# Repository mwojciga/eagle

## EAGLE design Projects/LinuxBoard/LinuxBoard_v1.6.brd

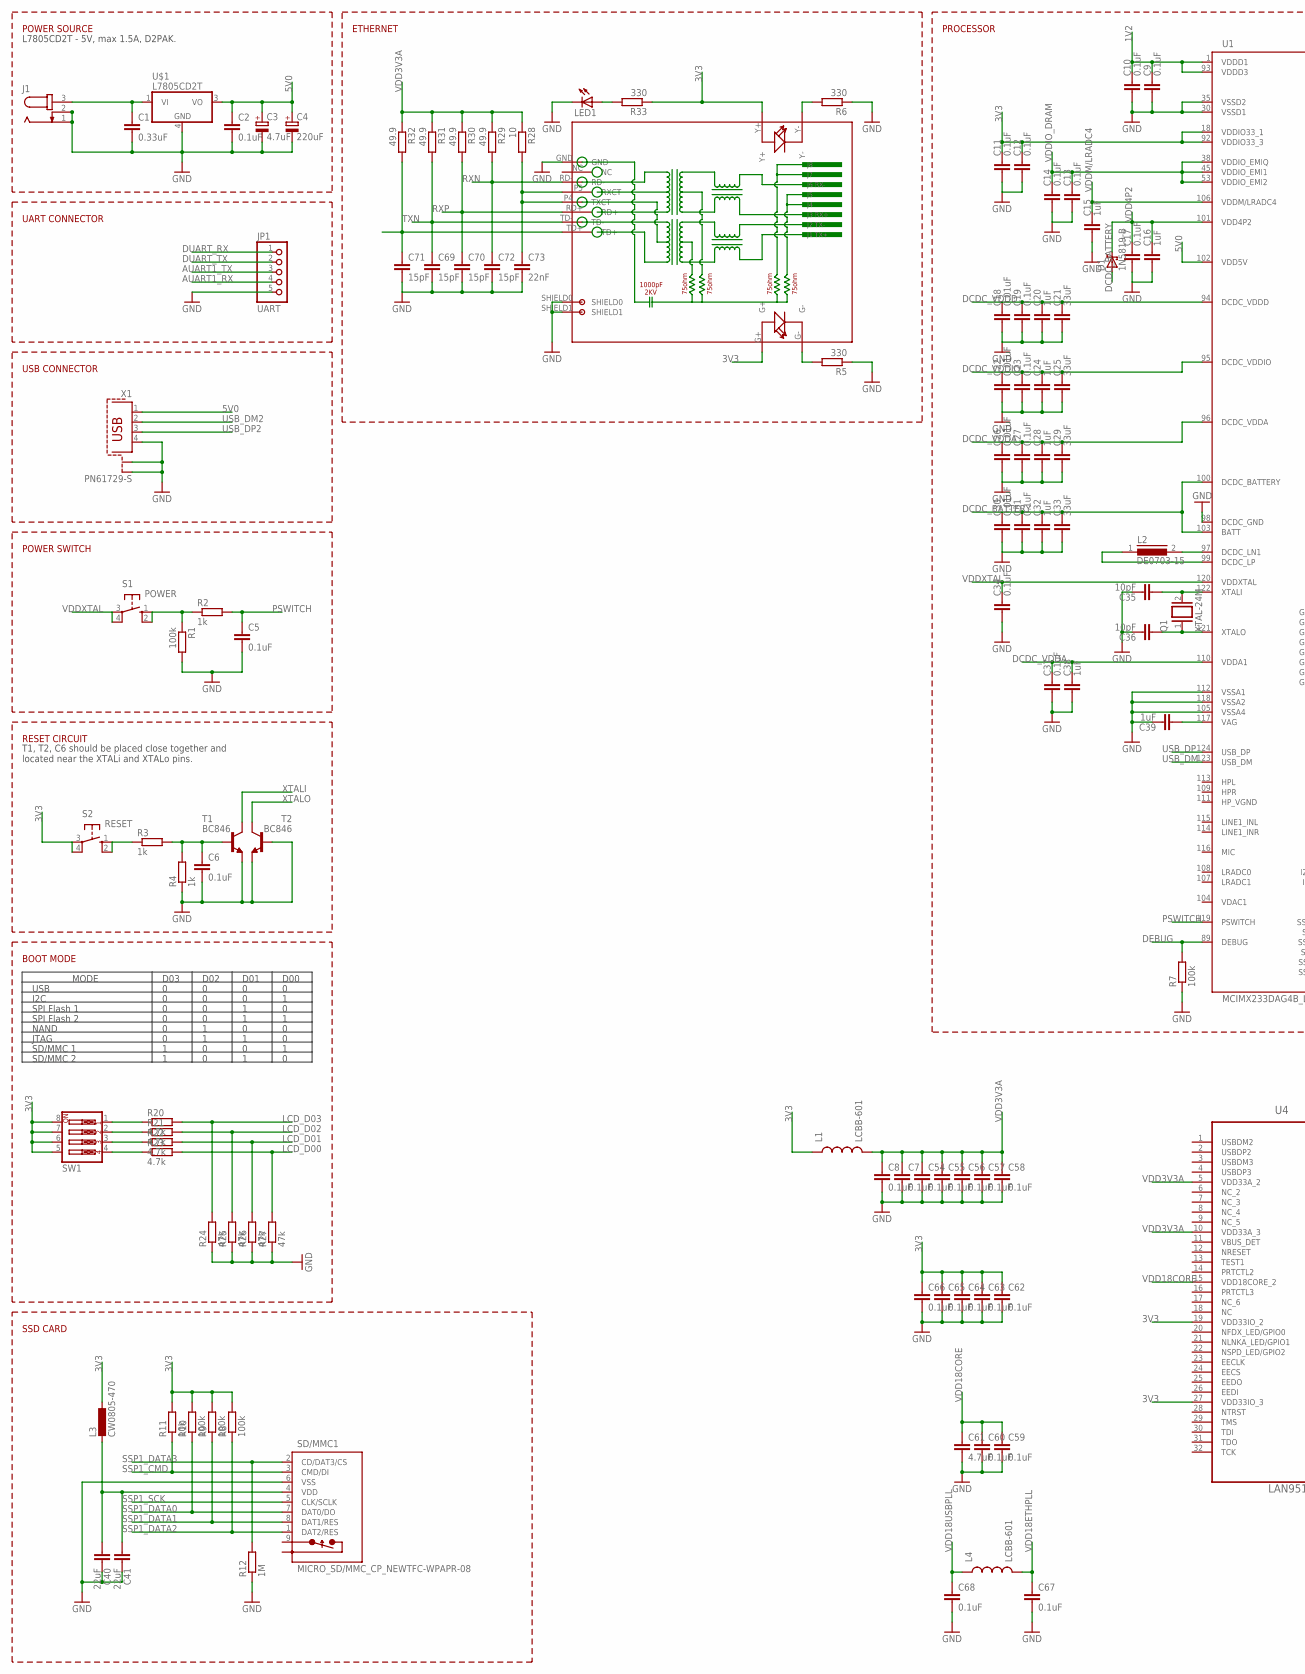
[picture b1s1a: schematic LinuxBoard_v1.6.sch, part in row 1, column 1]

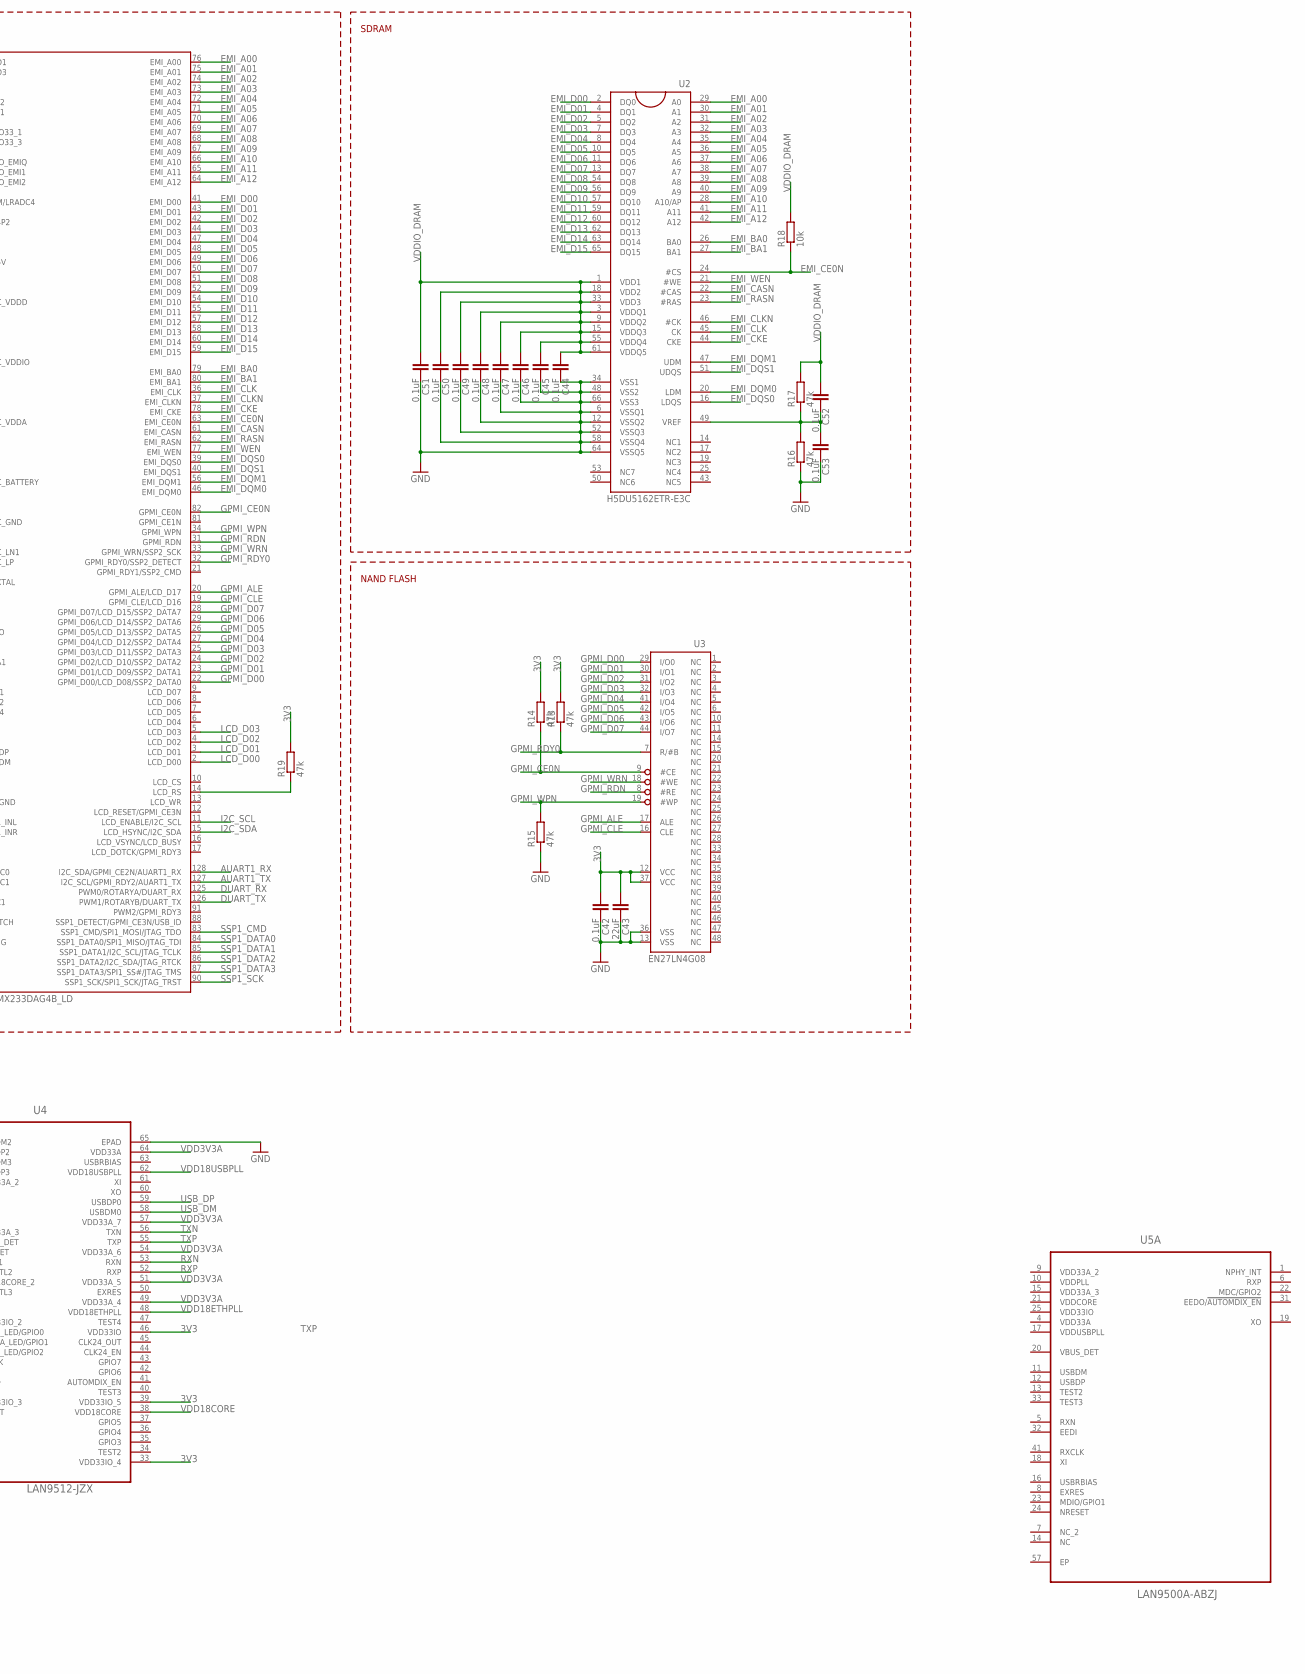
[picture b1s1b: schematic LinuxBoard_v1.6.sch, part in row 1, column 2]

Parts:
C1: 0.33uF; C0805
C2, C5, C6, C7, C8, C9, C10, C11, C12, C13, C14, C17, C19, C23, C27, C31, C34, C37, C42, C44, C45, C46, C47, C48, C49, C50, C51, C52, C53, C54, C55, C56, C57, C58, C59, C60, C62, C63, C64, C65, C66, C67, C68: 0.1uF; C0805
C3: 4.7uF; E2-5
C4: 220uF; E2-5
C15, C16, C20, C24, C28, C32, C38, C39: 1uF; C0805
C18, C22, C26, C30: 0.01uF; C0805
C21, C25, C29, C33: 33uF; C0805
C35, C36: 10pF; C0805
C40, C41, C43: 22uF; C0805
C61: 4.7uF; C0805
C69, C70, C71, C72: 15pF; C0805
C73: 22nF; C0805
D1: 1N5819-B; DO41-7.6
J1: JACK-PLUG0; SPC4077
JP1: UART; 1X05
L1, L4: LCBB-601; 0805
L2: DE0703-15; DR73
L3: CW0805-470; L2012C
LED1: LEDSML0805; SML0805
Q1: XTAL-24M; QS
R1, R7, R8, R9, R10: 100k; R0805
R2, R3, R4: 1k; R0805
R5, R6, R33: 330; R0805
R11, R18: 10k; R0805
R12: 1M; R0805
R13, R14, R15, R16, R17, R19, R24, R25, R26, R27: 47k; R0805
R20, R21, R22, R23: 4.7k; R0805
R28: 10; R0805
R29, R30, R31, R32: 49.9; R0805
RJ1: HR911105A
S1: POWER; B3F-10XX
S2: RESET; B3F-10XX
SD/MMC1: MICRO_SD/MMC_CP_NEWTFC-WPAPR-08; TFC-WPAPR-08
SW1: SW_DIP-4; EDG-04
T1, T2: BC846; SOT23
U1: MCIMX233DAG4B_LD; TQFP128LD
U2: H5DU5162ETR-E3C; 66TSOP-II
U3: EN27LN4G08; TSOP48
U4: LAN9512-JZX; QFN50P900X900X100-65N
U5: LAN9500A-ABZJ; QFN50P800X800X100-57N
U$1: L7805CD2T; D2PAK-3
X1: PN61729-S

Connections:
1V2: C9.1, C10.1, U1.1 (VDDD1), U1.93 (VDDD3)
3V3: C11.1, C12.1, C42.2, C43.2, C62.1, C63.1, C64.1, C65.1, C66.1, L1.1, L3.1, R8.2, R9.2, R10.2, R11.2, R13.2, R14.2, R19.2, R33.1, RJ1.G+, RJ1.Y+, S2.3, S2.4 (P1), SW1.5, SW1.6, SW1.7, SW1.8, U1.18 (VDDIO33_1), U1.92 (VDDIO33_3), U3.12 (VCC), U3.37 (VCC), U4.19 (VDD33IO_2), U4.27 (VDD33IO_3), U4.33 (VDD33IO_4), U4.39 (VDD33IO_5), U4.46 (VDD33IO)
5V0: C2.1, C3.+, C4.+, U1.102 (VDD5V), U$1.3 (VO), X1.1
AUART1_RX: JP1.4, U1.128 (I2C_SDA/GPMI_CE2N/AUART1_RX)
AUART1_TX: JP1.3, U1.127 (I2C_SCL/GPMI_RDY2/AUART1_TX)
DCDC_BATTERY: C30.1, C31.1, C32.1, C33.1, D1.A, U1.100 (DCDC_BATTERY), U1.103 (BATT)
DCDC_VDDA: C26.1, C27.1, C28.1, C29.1, C37.1, C38.1, U1.96 (DCDC_VDDA), U1.110 (VDDA1)
DCDC_VDDD: C18.1, C19.1, C20.1, C21.1, U1.94 (DCDC_VDDD)
DCDC_VDDIO: C22.1, C23.1, C24.1, C25.1, U1.95 (DCDC_VDDIO)
DEBUG: R7.2, U1.89 (DEBUG)
DUART_RX: JP1.1, U1.125 (PWM0/ROTARYA/DUART_RX)
DUART_TX: JP1.2, U1.126 (PWM1/ROTARYB/DUART_TX)
EMI_A00: U1.76 (EMI_A00), U2.29 (A0)
EMI_A01: U1.75 (EMI_A01), U2.30 (A1)
EMI_A02: U1.74 (EMI_A02), U2.31 (A2)
EMI_A03: U1.73 (EMI_A03), U2.32 (A3)
EMI_A04: U1.72 (EMI_A04), U2.35 (A4)
EMI_A05: U1.71 (EMI_A05), U2.36 (A5)
EMI_A06: U1.70 (EMI_A06), U2.37 (A6)
EMI_A07: U1.69 (EMI_A07), U2.38 (A7)
EMI_A08: U1.68 (EMI_A08), U2.39 (A8)
EMI_A09: U1.67 (EMI_A09), U2.40 (A9)
EMI_A10: U1.66 (EMI_A10), U2.28 (A10/AP)
EMI_A11: U1.65 (EMI_A11), U2.41 (A11)
EMI_A12: U1.64 (EMI_A12), U2.42 (A12)
EMI_BA0: U1.79 (EMI_BA0), U2.26 (BA0)
EMI_BA1: U1.80 (EMI_BA1), U2.27 (BA1)
EMI_CASN: U1.61 (EMI_CASN), U2.22 (#CAS)
EMI_CE0N: R18.1, U1.63 (EMI_CE0N), U2.24 (#CS)
EMI_CKE: U1.78 (EMI_CKE), U2.44 (CKE)
EMI_CLK: U1.36 (EMI_CLK), U2.45 (CK)
EMI_CLKN: U1.37 (EMI_CLKN), U2.46 (#CK)
EMI_D00: U1.41 (EMI_D00), U2.2 (DQ0)
EMI_D01: U1.43 (EMI_D01), U2.4 (DQ1)
EMI_D02: U1.42 (EMI_D02), U2.5 (DQ2)
EMI_D03: U1.44 (EMI_D03), U2.7 (DQ3)
EMI_D04: U1.47 (EMI_D04), U2.8 (DQ4)
EMI_D05: U1.48 (EMI_D05), U2.10 (DQ5)
EMI_D06: U1.49 (EMI_D06), U2.11 (DQ6)
EMI_D07: U1.50 (EMI_D07), U2.13 (DQ7)
EMI_D08: U1.51 (EMI_D08), U2.54 (DQ8)
EMI_D09: U1.52 (EMI_D09), U2.56 (DQ9)
EMI_D10: U1.54 (EMI_D10), U2.57 (DQ10)
EMI_D11: U1.55 (EMI_D11), U2.59 (DQ11)
EMI_D12: U1.57 (EMI_D12), U2.60 (DQ12)
EMI_D13: U1.58 (EMI_D13), U2.62 (DQ13)
EMI_D14: U1.60 (EMI_D14), U2.63 (DQ14)
EMI_D15: U1.59 (EMI_D15), U2.65 (DQ15)
EMI_DQM0: U1.46 (EMI_DQM0), U2.20 (LDM)
EMI_DQM1: U1.56 (EMI_DQM1), U2.47 (UDM)
EMI_DQS0: U1.39 (EMI_DQS0), U2.16 (LDQS)
EMI_DQS1: U1.40 (EMI_DQS1), U2.51 (UDQS)
EMI_RASN: U1.62 (EMI_RASN), U2.23 (#RAS)
EMI_WEN: U1.77 (EMI_WEN), U2.21 (#WE)
GND: C1.2, C2.2, C3.-, C4.-, C5.2, C6.2, C7.2, C8.2, C9.2, C10.2, C11.2, C12.2, C13.2, C14.2, C15.2, C16.2, C17.2, C18.2, C19.2, C20.2, C21.2, C22.2, C23.2, C24.2, C25.2, C26.2, C27.2, C28.2, C29.2, C30.2, C31.2, C32.2, C33.2, C34.2, C35.1, C36.1, C37.2, C38.2, C39.1, C40.1, C41.1, C42.1, C43.1, C44.1, C45.1, C46.1, C47.1, C48.1, C49.1, C50.1, C51.1, C53.1, C54.2, C55.2, C56.2, C57.2, C58.2, C59.2, C60.2, C61.2, C62.2, C63.2, C64.2, C65.2, C66.2, C67.2, C68.2, C69.2, C70.2, C71.2, C72.2, C73.2, J1.1, J1.2, JP1.5, LED1.C, R1.2, R4.1, R5.1, R6.1, R7.1, R12.1, R15.1, R16.1, R24.1, R25.1, R26.1, R27.1, RJ1.GND, RJ1.SHIELD0, RJ1.SHIELD1, SD/MMC1.6 (VSS), T1.2 (E), T2.1 (B), T2.2 (E), U1.30 (VSSD1), U1.35 (VSSD2), U1.98 (DCDC_GND), U1.105 (VSSA4), U1.112 (VSSA1), U1.118 (VSSA2), U2.6 (VSSQ1), U2.12 (VSSQ2), U2.34 (VSS1), U2.48 (VSS2), U2.52 (VSSQ3), U2.58 (VSSQ4), U2.64 (VSSQ5), U2.66 (VSS3), U3.13 (VSS), U3.36 (VSS), U4.65 (EPAD), U$1.4 (GND), X1.4, X1.S1, X1.S2
GPMI_ALE: U1.20 (GPMI_ALE/LCD_D17), U3.17 (ALE)
GPMI_CE0N: R14.1, U1.82 (GPMI_CE0N), U3.9 (#CE)
GPMI_CLE: U1.19 (GPMI_CLE/LCD_D16), U3.16 (CLE)
GPMI_D00: U1.22 (GPMI_D00/LCD_D08/SSP2_DATA0), U3.29 (I/O0)
GPMI_D01: U1.23 (GPMI_D01/LCD_D09/SSP2_DATA1), U3.30 (I/O1)
GPMI_D02: U1.24 (GPMI_D02/LCD_D10/SSP2_DATA2), U3.31 (I/O2)
GPMI_D03: U1.25 (GPMI_D03/LCD_D11/SSP2_DATA3), U3.32 (I/O3)
GPMI_D04: U1.27 (GPMI_D04/LCD_D12/SSP2_DATA4), U3.41 (I/O4)
GPMI_D05: U1.26 (GPMI_D05/LCD_D13/SSP2_DATA5), U3.42 (I/O5)
GPMI_D06: U1.29 (GPMI_D06/LCD_D14/SSP2_DATA6), U3.43 (I/O6)
GPMI_D07: U1.28 (GPMI_D07/LCD_D15/SSP2_DATA7), U3.44 (I/O7)
GPMI_RDN: U1.31 (GPMI_RDN), U3.8 (#RE)
GPMI_RDY0: R13.1, U1.32 (GPMI_RDY0/SSP2_DETECT), U3.7 (R/#B)
GPMI_WPN: R15.2, U1.34 (GPMI_WPN), U3.19 (#WP)
GPMI_WRN: U1.33 (GPMI_WRN/SSP2_SCK), U3.18 (#WE)
HP_VGND: U1.111 (HP_VGND)
I2C_SCL: U1.11 (LCD_ENABLE/I2C_SCL)
I2C_SDA: U1.15 (LCD_HSYNC/I2C_SDA)
LCD_D00: R23.2, R27.2, U1.2 (LCD_D00)
LCD_D01: R22.2, R26.2, U1.3 (LCD_D01)
LCD_D02: R21.2, R25.2, U1.4 (LCD_D02)
LCD_D03: R20.2, R24.2, U1.5 (LCD_D03)
unnamed: C1.1, J1.3, U$1.1 (VI)
unnamed: R3.1, S2.1 (S), S2.2 (S1)
unnamed: R1.1, R2.1, S1.1 (S), S1.2 (S1)
unnamed: C6.1, R3.2, R4.2, T1.1 (B)
unnamed: R20.1, SW1.1
unnamed: R21.1, SW1.2
unnamed: R22.1, SW1.3
unnamed: R23.1, SW1.4
unnamed: L2.2, U1.97 (DCDC_LN1)
unnamed: R5.2, RJ1.G-
unnamed: L2.1, U1.99 (DCDC_LP)
unnamed: C39.2, U1.117 (VAG)
unnamed: R19.1, U1.14 (LCD_RS)
unnamed: R6.2, RJ1.Y-
unnamed: C40.2, C41.2, L3.2, SD/MMC1.4 (VDD)
unnamed: C73.1, R28.2, RJ1.P4 (TXCT), RJ1.P5 (RXCT)
unnamed: LED1.A, R33.2
unnamed: C52.1, C53.2, R16.2, R17.1, U2.49 (VREF)
PSWITCH: C5.1, R2.2, U1.119 (PSWITCH)
RXN: C72.1, R29.2, RJ1.RD-, U4.53 (RXN)
RXP: C70.1, R30.2, RJ1.RD+, U4.52 (RXP)
SSP1_CMD: R11.1, SD/MMC1.3 (CMD/DI), U1.83 (SSP1_CMD/SPI1_MOSI/JTAG_TDO)
SSP1_DATA0: R10.1, SD/MMC1.7 (DAT0/DO), U1.84 (SSP1_DATA0/SPI1_MISO/JTAG_TDI)
SSP1_DATA1: R9.1, SD/MMC1.8 (DAT1/RES), U1.85 (SSP1_DATA1/I2C_SCL/JTAG_TCLK)
SSP1_DATA2: R8.1, SD/MMC1.1 (DAT2/RES), U1.86 (SSP1_DATA2/I2C_SDA/JTAG_RTCK)
SSP1_DATA3: R12.2, SD/MMC1.2 (CD/DAT3/CS), U1.87 (SSP1_DATA3/SPI1_SS#/JTAG_TMS)
SSP1_SCK: SD/MMC1.5 (CLK/SCLK), U1.90 (SSP1_SCK/SPI1_SCK/JTAG_TRST)
TEST1: U5.49 (TEST1)
TEST2: U5.13 (TEST2)
TEST3: U5.33 (TEST3)
TXN: C69.1, R31.2, RJ1.TD-, U4.56 (TXN)
TXP: C71.1, R32.2, RJ1.TD+, U4.55 (TXP)
USB_DM: U1.123 (USB_DM), U4.58 (USBDM0)
USB_DM2: X1.2
USB_DP: U1.124 (USB_DP), U4.59 (USBDP0)
USB_DP2: X1.3
VBUS_DET: U4.11 (VBUS_DET), U5.20 (VBUS_DET)
VDD3V3A: C7.1, C8.1, C54.1, C55.1, C56.1, C57.1, C58.1, L1.2, R28.1, R29.1, R30.1, R31.1, R32.1, U4.5 (VDD33A_2), U4.10 (VDD33A_3), U4.49 (VDD33A_4), U4.51 (VDD33A_5), U4.54 (VDD33A_6), U4.57 (VDD33A_7), U4.64 (VDD33A), U5.4 (VDD33A)
VDD4P2: C16.1, C17.1, D1.C, U1.101 (VDD4P2)
VDD18CORE: C59.1, C60.1, C61.1, U4.15 (VDD18CORE_2), U4.38 (VDD18CORE)
VDD18ETHPLL: C67.1, L4.2, U4.48 (VDD18ETHPLL)
VDD18USBPLL: C68.1, L4.1, U4.62 (VDD18USBPLL)
VDD33A_2: U5.9 (VDD33A_2)
VDD33A_3: U5.15 (VDD33A_3)
VDD33IO: U5.25 (VDD33IO), U5.52 (VDD33IO)
VDD33IO_2: U5.48 (VDD33IO_2)
VDD33IO_3: U5.51 (VDD33IO_3)
VDD33IO_4: U5.35 (VDD33IO_4)
VDDCORE: U5.50 (VDDCORE)
VDDIO_DRAM: C13.1, C14.1, C44.2, C45.2, C46.2, C47.2, C48.2, C49.2, C50.2, C51.2, C52.2, R17.2, R18.2, U1.38 (VDDIO_EMIQ), U1.45 (VDDIO_EMI1), U1.53 (VDDIO_EMI2), U2.1 (VDD1), U2.3 (VDDQ1), U2.9 (VDDQ2), U2.15 (VDDQ3), U2.18 (VDD2), U2.33 (VDD3), U2.55 (VDDQ4), U2.61 (VDDQ5)
VDDM/LRADC4: C15.1, U1.106 (VDDM/LRADC4)
VDDPLL: U5.10 (VDDPLL)
VDDUSBPLL: U5.17 (VDDUSBPLL)
VDDXTAL: C34.1, S1.3, S1.4 (P1), U1.120 (VDDXTAL)
XTALI: C35.2, Q1.2, T1.3 (C), U1.122 (XTALI)
XTALO: C36.2, Q1.1, T2.3 (C), U1.121 (XTALO)

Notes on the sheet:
L7805CD2T - 5V, max 1.5A, D2PAK.
POWER SOURCE
UART CONNECTOR
USB CONNECTOR
POWER SWITCH
RESET CIRCUIT
T1, T2, C6 should be placed close together and located near the XTALi and XTALo pins.
BOOT MODE
MODE
D03
D02
D01
D00
USB
I2C
SPI Flash 1
SPI Flash 2
NAND
JTAG
SD/MMC 1
SD/MMC 2
SSD CARD
SDRAM
NAND FLASH
ETHERNET
PROCESSOR

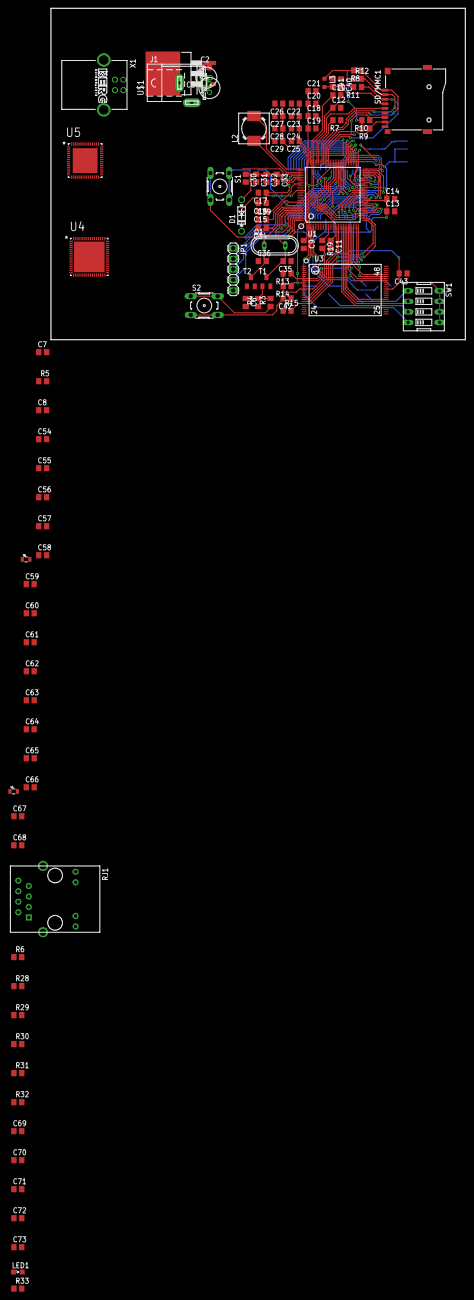
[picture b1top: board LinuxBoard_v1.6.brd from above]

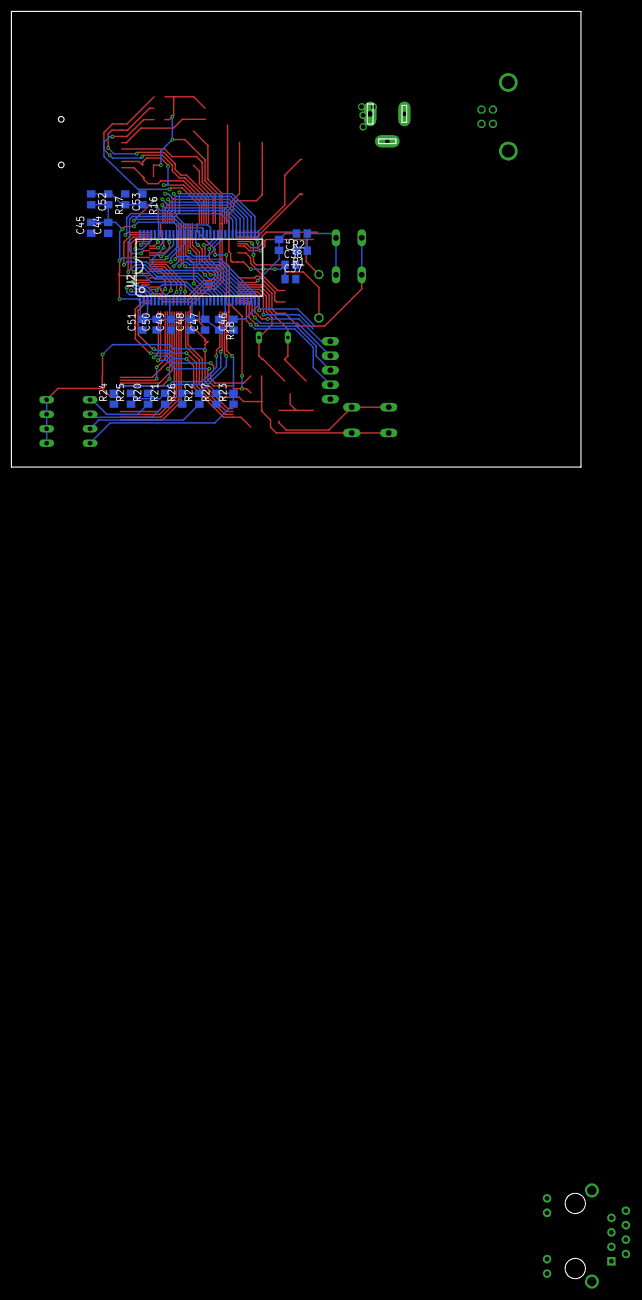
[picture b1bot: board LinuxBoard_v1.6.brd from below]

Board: 2 copper layers, 100.0 x 80.0 mm, 129 parts (27 on the bottom side), 117 nets.

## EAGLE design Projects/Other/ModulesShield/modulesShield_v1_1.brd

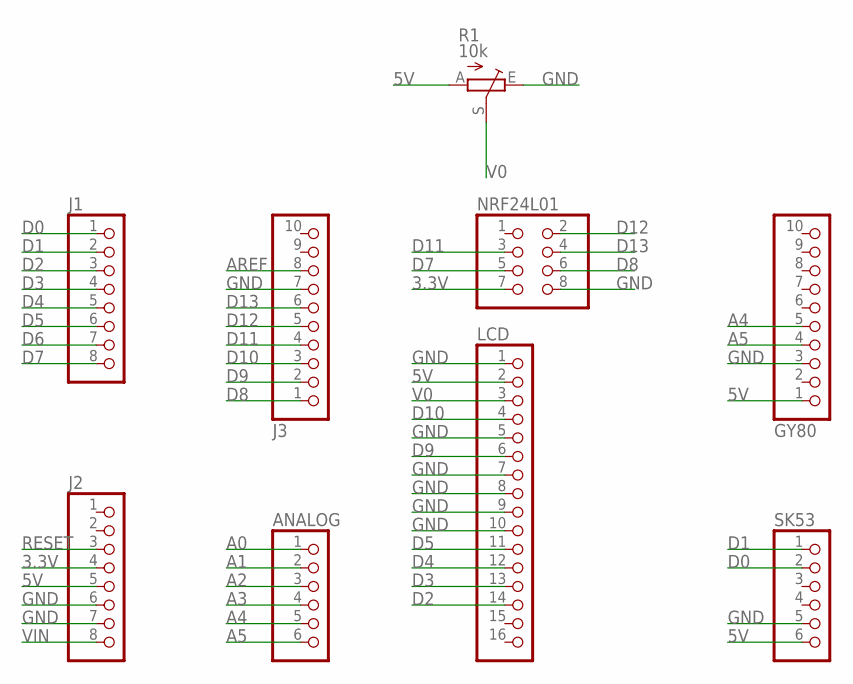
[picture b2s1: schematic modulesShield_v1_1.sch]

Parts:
ANALOG: PINHD-1X6; 1X06
GY80: PINHD-1X10TH; 1X10-TH
J1, J2: PINHD-1X8TH; 1X08-TH
J3: PINHD-1X10TH; 1X10-TH
LCD: PINHD-1X16; 1X16
NRF24L01: PINHD-2X4; 2X04
R1: 10k; CA6V
SK53: PINHD-1X6; 1X06

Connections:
3.3V: J2.4, NRF24L01.7
5V: GY80.1, J2.5, LCD.2, R1.A, SK53.6
A0: ANALOG.1
A1: ANALOG.2
A2: ANALOG.3
A3: ANALOG.4
A4: ANALOG.5, GY80.5
A5: ANALOG.6, GY80.4
AREF: J3.8
D0: J1.1, SK53.2
D1: J1.2, SK53.1
D2: J1.3, LCD.14
D3: J1.4, LCD.13
D4: J1.5, LCD.12
D5: J1.6, LCD.11
D6: J1.7
D7: J1.8, NRF24L01.5
D8: J3.1, NRF24L01.6
D9: J3.2, LCD.6
D10: J3.3, LCD.4
D11: J3.4, NRF24L01.3
D12: J3.5, NRF24L01.2
D13: J3.6, NRF24L01.4
GND: GY80.3, J2.6, J2.7, J3.7, LCD.1, LCD.5, LCD.7, LCD.8, LCD.9, LCD.10, NRF24L01.8, R1.E, SK53.5
RESET: J2.3
V0: LCD.3, R1.S
VIN: J2.8

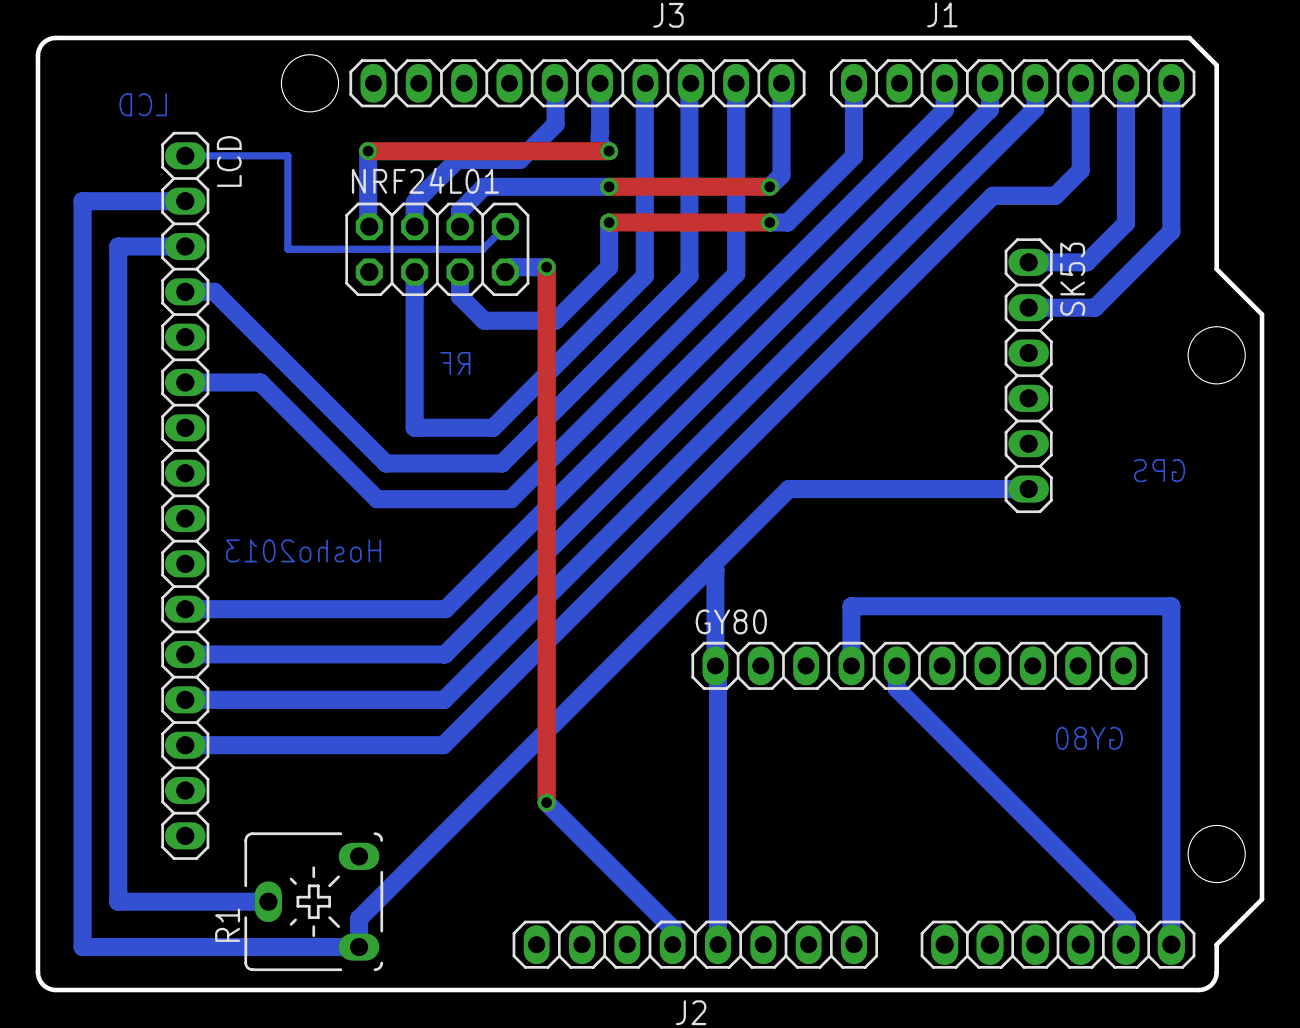
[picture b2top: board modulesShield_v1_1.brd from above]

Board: 2 copper layers, 68.6 x 53.3 mm, 9 parts (0 on the bottom side), 19 nets.

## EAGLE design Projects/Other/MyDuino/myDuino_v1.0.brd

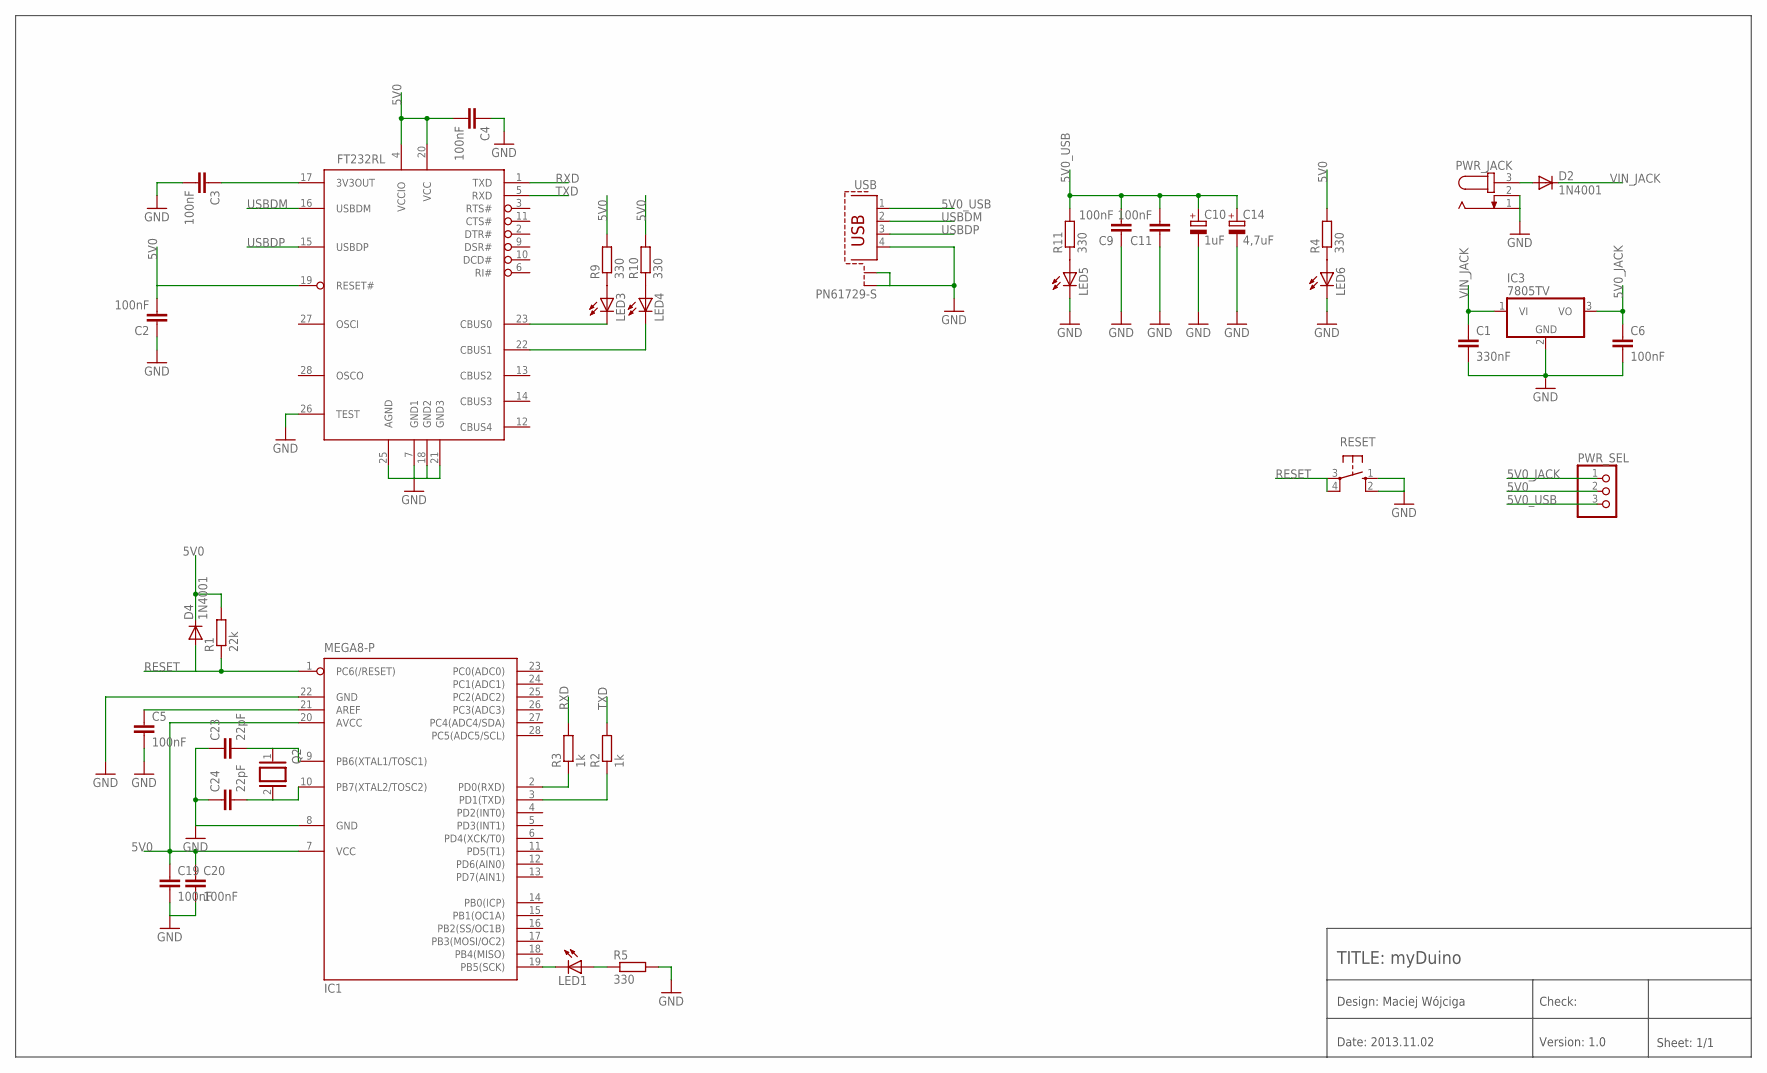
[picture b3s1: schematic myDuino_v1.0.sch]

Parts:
C1: 330nF; C025-025X050
C2, C3, C4, C5, C6, C9, C11, C19, C20: 100nF; C025-025X050
C10: 1uF; E2,5-5
C14: 4,7uF; E2,5-5
C23, C24: 22pF; C025-025X050
D2, D4: 1N4001; DO41-10
FT232RL: FT232RL; SSOP28DB
IC1: MEGA8-P; DIL28-3
IC3: 7805TV; TO220V
LED1, LED3, LED4, LED5, LED6: LED3MM
PWR_JACK: JACK-PLUG0; SPC4077
PWR_SEL: PINHD-1X3; 1X03
Q2: XTAL/S; QS
R1: 22k; 0207/10
R2, R3: 1k; 0207/10
R4, R5, R9, R10, R11: 330; 0207/10
RESET: 10-XX; B3F-10XX
USB: PN61729-S

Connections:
5V0: C2.2, C4.2, C19.1, C20.1, D4.C, FT232RL.4 (VCCIO), FT232RL.19 (RESET#), FT232RL.20 (VCC), IC1.7 (VCC), IC1.20 (AVCC), PWR_SEL.2, R1.2, R4.2, R9.2, R10.2
5V0_JACK: C6.1, IC3.3 (VO), PWR_SEL.1
5V0_USB: C9.2, C10.+, C11.2, C14.+, PWR_SEL.3, R11.2, USB.1
GND: C1.2, C2.1, C3.2, C4.1, C5.2, C6.2, C9.1, C10.-, C11.1, C14.-, C19.2, C20.2, C23.1, C24.1, FT232RL.7 (GND1), FT232RL.18 (GND2), FT232RL.21 (GND3), FT232RL.25 (AGND), FT232RL.26 (TEST), IC1.8 (GND), IC1.22 (GND), IC3.2 (GND), LED5.K (C), LED6.K (C), PWR_JACK.1, PWR_JACK.2, R5.2, RESET.1 (S), RESET.2 (S1), USB.4, USB.S1, USB.S2
unnamed: IC1.3 (PD1(TXD)), R2.1
unnamed: IC1.2 (PD0(RXD)), R3.1
unnamed: LED6.A, R4.1
unnamed: D2.A, PWR_JACK.3
unnamed: LED1.A, R5.1
unnamed: IC1.19 (PB5(SCK)), LED1.K (C)
unnamed: LED3.A, R9.1
unnamed: LED4.A, R10.1
unnamed: LED5.A, R11.1
unnamed: C5.1, IC1.21 (AREF)
unnamed: C23.2, IC1.9 (PB6(XTAL1/TOSC1)), Q2.1
unnamed: C24.2, IC1.10 (PB7(XTAL2/TOSC2)), Q2.2
unnamed: FT232RL.23 (CBUS0), LED3.K (C)
unnamed: FT232RL.22 (CBUS1), LED4.K (C)
unnamed: C3.1, FT232RL.17 (3V3OUT)
RESET: D4.A, IC1.1 (PC6(/RESET)), R1.1, RESET.3, RESET.4 (P1)
RXD: FT232RL.1 (TXD), R3.2
TXD: FT232RL.5 (RXD), R2.2
USBDM: FT232RL.16 (USBDM), USB.2
USBDP: FT232RL.15 (USBDP), USB.3
VIN_JACK: C1.1, D2.C, IC3.1 (VI)

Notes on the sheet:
TITLE: myDuino
Design: Maciej Wójciga
Check:
Date: 2013.11.02
Version: 1.0
Sheet: 1/1

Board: 2 copper layers, 37 parts (0 on the bottom side), 25 nets, no tracks yet.

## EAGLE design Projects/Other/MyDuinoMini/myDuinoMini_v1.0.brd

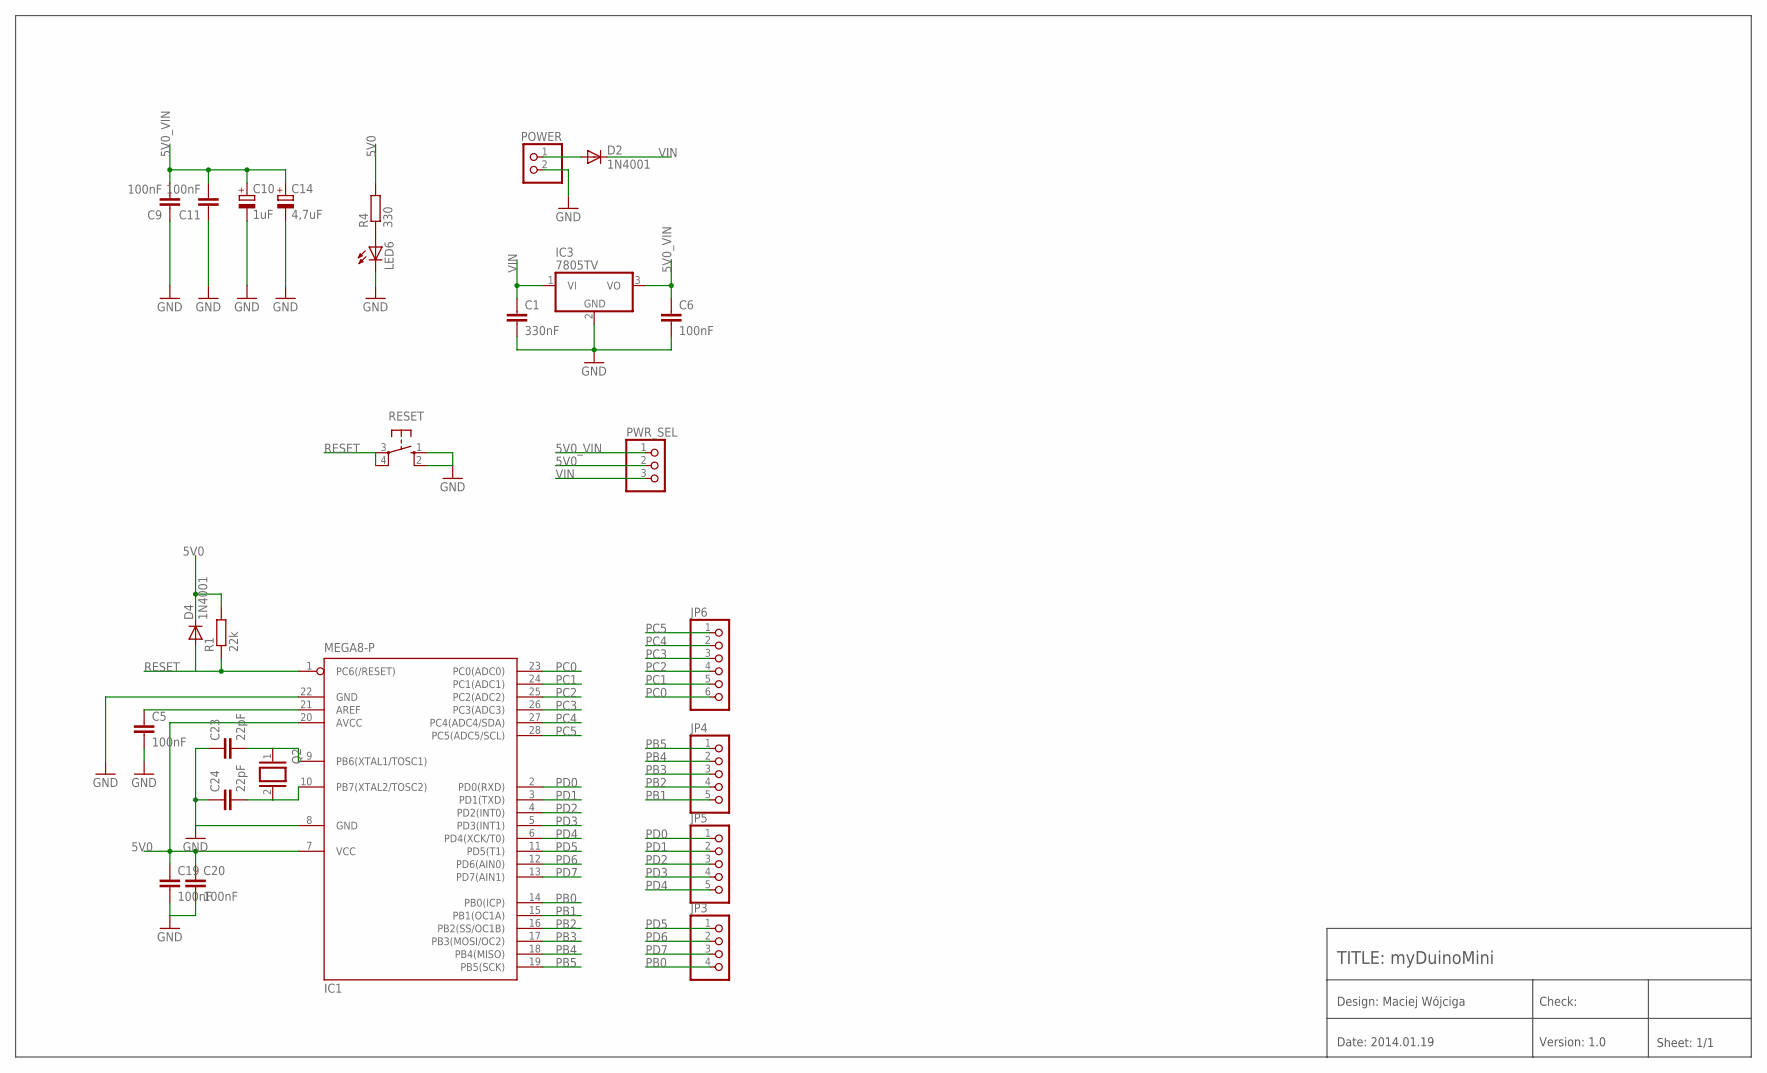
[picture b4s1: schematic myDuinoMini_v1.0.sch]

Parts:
C1: 330nF; C025-025X050
C5, C6, C9, C11, C19, C20: 100nF; C025-025X050
C10: 1uF; E2,5-5
C14: 4,7uF; E2,5-5
C23, C24: 22pF; C025-025X050
D2, D4: 1N4001; DO41-10
IC1: MEGA8-P; DIL28-3
IC3: 7805TV; TO220V
JP3: PINHD-1X4; 1X04
JP4, JP5: PINHD-1X5; 1X05
JP6: PINHD-1X6; 1X06
LED6: LED3MM
POWER: PINHD-1X2; 1X02
PWR_SEL: PINHD-1X3; 1X03
Q2: XTAL/S; QS
R1: 22k; 0207/10
R4: 330; 0207/10
RESET: 10-XX; B3F-10XX

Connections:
5V0: C19.1, C20.1, D4.C, IC1.7 (VCC), IC1.20 (AVCC), PWR_SEL.2, R1.2, R4.2
5V0_VIN: C6.1, C9.2, C10.+, C11.2, C14.+, IC3.3 (VO), PWR_SEL.1
GND: C1.2, C5.2, C6.2, C9.1, C10.-, C11.1, C14.-, C19.2, C20.2, C23.1, C24.1, IC1.8 (GND), IC1.22 (GND), IC3.2 (GND), LED6.K (C), POWER.2, RESET.1 (S), RESET.2 (S1)
unnamed: LED6.A, R4.1
unnamed: D2.A, POWER.1
unnamed: C5.1, IC1.21 (AREF)
unnamed: C23.2, IC1.9 (PB6(XTAL1/TOSC1)), Q2.1
unnamed: C24.2, IC1.10 (PB7(XTAL2/TOSC2)), Q2.2
PB0: IC1.14 (PB0(ICP)), JP3.4
PB1: IC1.15 (PB1(OC1A)), JP4.5
PB2: IC1.16 (PB2(SS/OC1B)), JP4.4
PB3: IC1.17 (PB3(MOSI/OC2)), JP4.3
PB4: IC1.18 (PB4(MISO)), JP4.2
PB5: IC1.19 (PB5(SCK)), JP4.1
PC0: IC1.23 (PC0(ADC0)), JP6.6
PC1: IC1.24 (PC1(ADC1)), JP6.5
PC2: IC1.25 (PC2(ADC2)), JP6.4
PC3: IC1.26 (PC3(ADC3)), JP6.3
PC4: IC1.27 (PC4(ADC4/SDA)), JP6.2
PC5: IC1.28 (PC5(ADC5/SCL)), JP6.1
PD0: IC1.2 (PD0(RXD)), JP5.1
PD1: IC1.3 (PD1(TXD)), JP5.2
PD2: IC1.4 (PD2(INT0)), JP5.3
PD3: IC1.5 (PD3(INT1)), JP5.4
PD4: IC1.6 (PD4(XCK/T0)), JP5.5
PD5: IC1.11 (PD5(T1)), JP3.1
PD6: IC1.12 (PD6(AIN0)), JP3.2
PD7: IC1.13 (PD7(AIN1)), JP3.3
RESET: D4.A, IC1.1 (PC6(/RESET)), R1.1, RESET.3, RESET.4 (P1)
VIN: C1.1, D2.C, IC3.1 (VI), PWR_SEL.3

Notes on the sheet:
TITLE: myDuinoMini
Design: Maciej Wójciga
Check:
Date: 2014.01.19
Version: 1.0
Sheet: 1/1

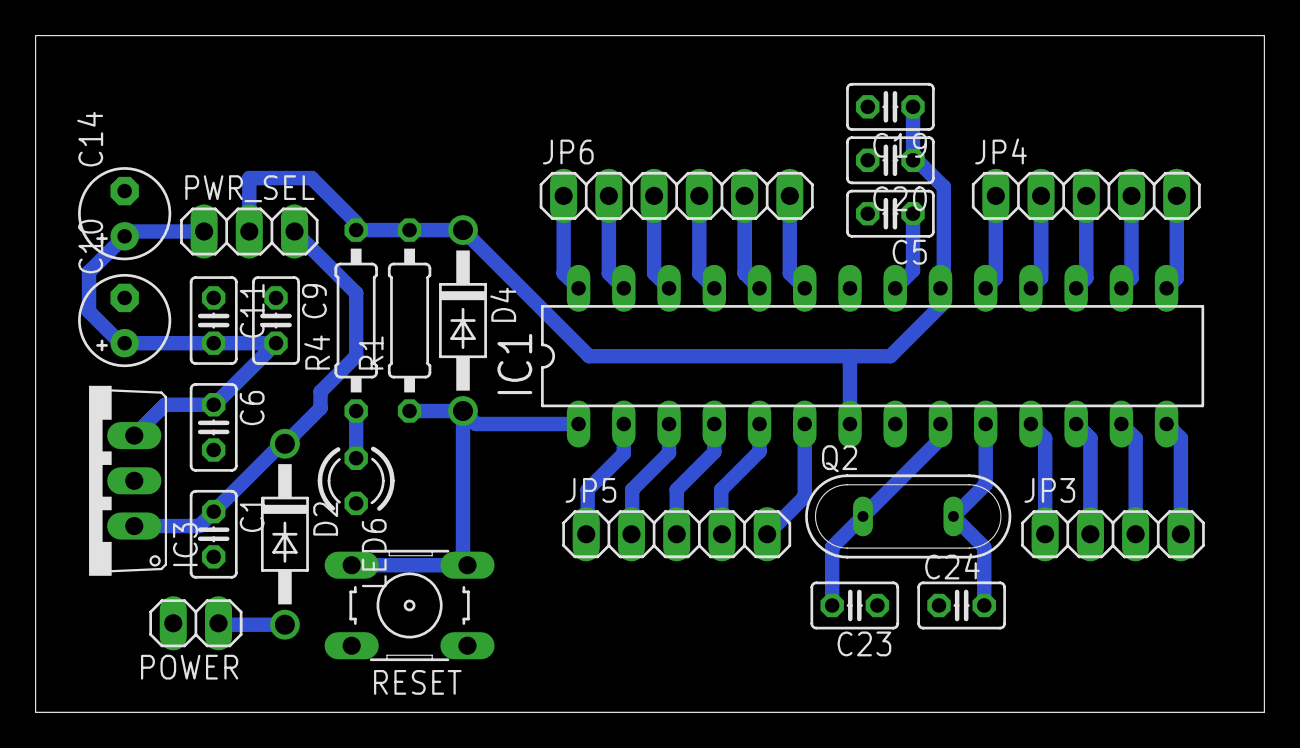
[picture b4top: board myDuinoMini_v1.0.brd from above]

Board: 2 copper layers, 69.0 x 38.0 mm, 26 parts (0 on the bottom side), 30 nets.

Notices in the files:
parts and their libraries:
SparkFun-Passives: Licensing: Creative Commons ShareAlike 4.0 International - https://creativecommons.org/licenses/by-sa/4.0
